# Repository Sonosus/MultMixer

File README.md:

# MultMixer
[![CC BY-SA 4.0][cc-by-sa-shield]][cc-by-sa]

This is a Kosmo format module that is a combined buffered multiple and mixer. 
The multiple section has 1 input, 5 outputs, and an LED. The input is buffered to the 5 outputs, and the LED is used to show the state of the signal.

In the mixer section, there are 5 inputs and one output. Each input has its own pot and switch. The pot acts as an attenuator, and the switch disconnects that input from the main output. 

This module is based on the [LMNC Buffered Multiple](https://www.lookmumnocomputer.com/1161-buffered-multiple) and the [LMNC Mini Mixer](https://www.lookmumnocomputer.com/projects#/1163-mini-mixer). Much credit to Sam for open-sourcing his modules!

Interactive BOM [here](https://htmlpreview.github.io/?https://github.com/Sonosus/MultMixer/blob/main/Docs/MultMixer.html)

This work is licensed under a
[Creative Commons Attribution-ShareAlike 4.0 International License][cc-by-sa].

[![CC BY-SA 4.0][cc-by-sa-image]][cc-by-sa]

[cc-by-sa]: http://creativecommons.org/licenses/by-sa/4.0/
[cc-by-sa-image]: https://licensebuttons.net/l/by-sa/4.0/88x31.png
[cc-by-sa-shield]: https://img.shields.io/badge/License-CC%20BY--SA%204.0-lightgrey.svg

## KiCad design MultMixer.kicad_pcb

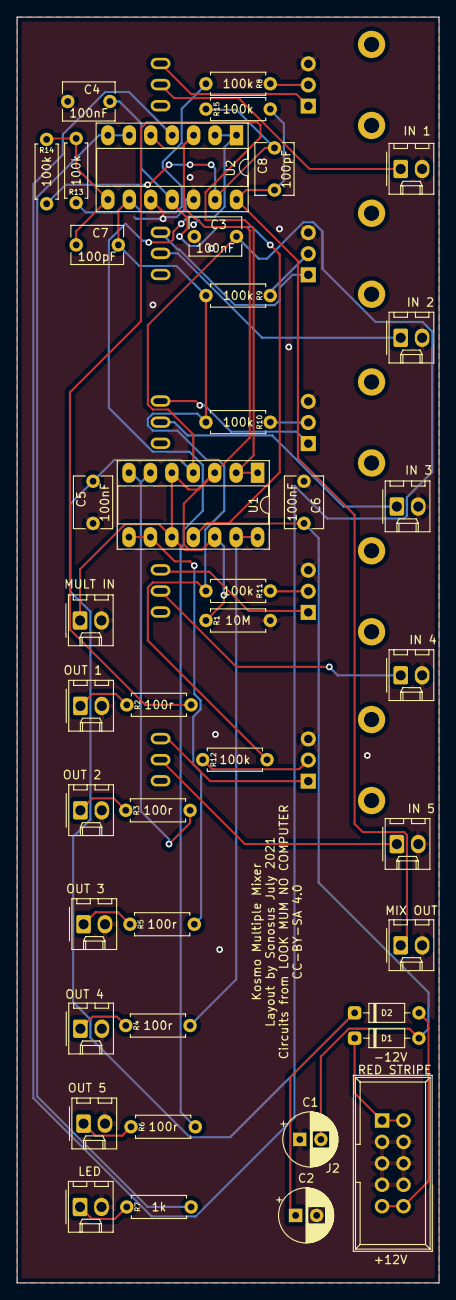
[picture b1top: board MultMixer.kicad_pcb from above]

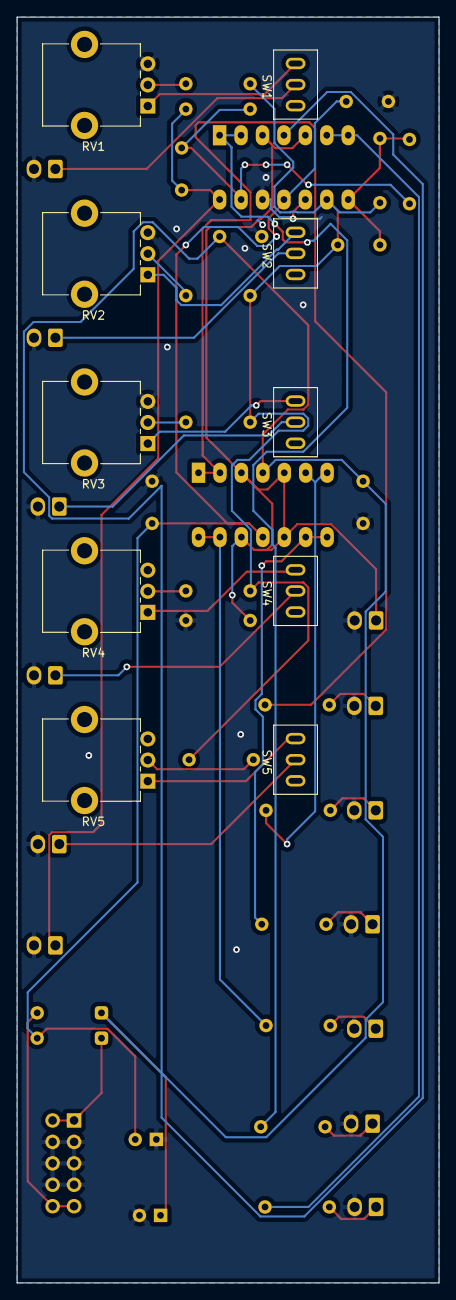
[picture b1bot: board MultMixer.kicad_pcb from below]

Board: 2 copper layers, 50.0 x 150.0 mm, 51 parts (10 on the bottom side), 37 nets.

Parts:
C1, C2: 10uF; Capacitor_Polarized
C3, C4, C5, C6: 100nF; Capacitor_NonPolarized
C7, C8: 100pF; Capacitor_NonPolarized
D1, D2: 1N5817; Diode_DO-35
IN 1: In 1; Molex_KK-254_AE-6410-02A_1x02_P2.54mm_Vertical
IN 2: In 2; Molex_KK-254_AE-6410-02A_1x02_P2.54mm_Vertical
IN 3: In 3; Molex_KK-254_AE-6410-02A_1x02_P2.54mm_Vertical
IN 4: In 4; Molex_KK-254_AE-6410-02A_1x02_P2.54mm_Vertical
IN 5: In 5; Molex_KK-254_AE-6410-02A_1x02_P2.54mm_Vertical
J2: Conn_02x05_Odd_Even; Power_Header
LED: LED; Molex_KK-254_AE-6410-02A_1x02_P2.54mm_Vertical
MIX OUT: Mixer Out; Molex_KK-254_AE-6410-02A_1x02_P2.54mm_Vertical
MULT IN: Mult IN; Molex_KK-254_AE-6410-02A_1x02_P2.54mm_Vertical
OUT 1: Out 1; Molex_KK-254_AE-6410-02A_1x02_P2.54mm_Vertical
OUT 2: Out 2; Molex_KK-254_AE-6410-02A_1x02_P2.54mm_Vertical
OUT 3: Out 3; Molex_KK-254_AE-6410-02A_1x02_P2.54mm_Vertical
OUT 4: Out 4; Molex_KK-254_AE-6410-02A_1x02_P2.54mm_Vertical
OUT 5: Out 5; Molex_KK-254_AE-6410-02A_1x02_P2.54mm_Vertical
R1: 10M; Resistor
R2, R3, R4, R5, R6: 100r; Resistor
R7: 1k; Resistor
R8, R9, R10, R11, R12, R13, R14, R15: 100k; Resistor
RV1, RV2, RV3, RV4, RV5: 100k; Potentiometer_Alpha_RD901F-40-00D_centred
SW1, SW2, SW3, SW4, SW5: on/off; SPST_Toggle_A-3643
U1, U2: TL074; DIP-14_Socket

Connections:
+12V: C2.1, C3.2, C5.2, D2.1, U1.4, U2.4
-12V: C1.2, C4.2, C6.2, D1.2, U1.11, U2.11
GND: C1.1, C2.2, C3.1, C4.1, C5.1, C6.1, IN 1.2, IN 2.2, IN 3.2, IN 4.2, IN 5.2, J2.3, J2.4, J2.5, J2.6, J2.7, J2.8, LED.1, MIX OUT.2, MULT IN.2, OUT 1.2, OUT 2.2, OUT 3.2, OUT 4.2, OUT 5.2, R1.2, RV1.3, RV2.3, RV3.3, RV4.3, RV5.3, U2.10, U2.12
unnamed: C7.1, R13.2, R14.1, U2.8
unnamed: C7.2, R8.2, R9.2, R10.2, R11.2, R12.2, R13.1, U2.9
unnamed: C8.1, MIX OUT.1, R15.2, U2.14
unnamed: C8.2, R14.2, R15.1, U2.13
unnamed: D1.1, J2.1, J2.2
unnamed: D2.2, J2.9, J2.10
unnamed: LED.2, R7.1
unnamed: MULT IN.1, R1.1, U1.3, U1.5, U1.10, U1.12, U2.3, U2.5
unnamed: OUT 1.1, R2.1
unnamed: OUT 2.1, R3.1
unnamed: OUT 4.1, R4.1
unnamed: OUT 3.1, R5.1
unnamed: OUT 5.1, R6.1
unnamed: IN 1.1, SW1.2
unnamed: IN 2.1, SW2.2
unnamed: IN 3.1, SW3.2
unnamed: IN 4.1, SW4.2
unnamed: IN 5.1, SW5.2
unnamed: R2.2, U1.1, U1.2
unnamed: R3.2, U1.6, U1.7
unnamed: R4.2, U1.13, U1.14
unnamed: R5.2, U1.8, U1.9
unnamed: R6.2, U2.1, U2.2
unnamed: R7.2, U2.6, U2.7
unnamed: R8.1, RV1.2
unnamed: R9.1, RV2.2
unnamed: R10.1, RV3.2
unnamed: R11.1, RV4.2
unnamed: R12.1, RV5.2
unnamed: RV1.1, SW1.1
unnamed: RV2.1, SW2.1
unnamed: RV3.1, SW3.1
unnamed: RV4.1, SW4.1
unnamed: RV5.1, SW5.1

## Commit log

2021-06-30 init kicad project
2021-06-30 symbol cache
2021-06-30 add power header
2021-06-30 mult section
2021-06-30 op amp power
2021-06-30 start mixer section
2021-06-30 mixer section
2021-06-30 mixer power
2021-06-30 annotate and finish schem!
2021-06-30 place pots
2021-07-01 shuffling
2021-07-01 output jack
2021-07-01 back annotate
2021-07-01 update pcb
2021-07-01 relabel output
2021-07-02 almost done
2021-07-02 silksmooth
2021-07-02 schematic plot
2021-07-02 plot gerbers
2021-07-02 zip gerbers
2021-07-02 interactive bom
2021-07-02 silkscreen text
2021-07-02 ibom
2021-07-02 save
